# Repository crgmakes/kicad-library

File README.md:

# CRG Makes KiCad Library

This repo contains all the KiCad symbols, footprints, models, and other files supporting [CRG Makes](https://crgmakes.com) development within KiCad.

## Installation

To install this library, start by [cloning](https://docs.github.com/en/repositories/creating-and-managing-repositories/cloning-a-repository) the [CRG Makes libary](https://github.com/crgmakes/kicad-library) repo to a convienent local directory.

In this example, our local directory will be: `/Users/Development/KiCad/CRGM/`. 

<div class="alert alert-info">
  <i class="fas fa-exclamation-triangle"></i> <strong>Note:</strong> Replace this value with absolute path of where you place <b><i>your</i></b> library.
</div>

Start by setting the base parameters, the schematic parameters, and finally PCB parameters.

### Set Base Parameters

Within KiCad Project viewer:

Click on Preferences->Configure Paths...

Perform the following actions:

1. Click "+" near the bottom
1. Type "KICAD_USER_LIBRARY" in the first cell
1. Paste the local location repo's root directory (i.e., `/Users/Development/KiCad/CRGM/`)
1. Click "+" near the bottom
1. In the first cell, type "KICAD_USER_MODEL_DIR"
1. In the second cell, paste "${KICAD_USER_LIBRARY}/models"
1. Click "+" near the bottom
1. In the first cell, type "KICAD_USER_TEMPLATE_DIR"
1. In the second cell, paste "${KICAD_USER_LIBRARY}/templates"

Your screen should look something like this:

Click OK to save.

### Schematic

Within KiCad Schematic Editor, click Preferences->Manage Symbol Libraries...

Add the following parameters by clicking +:

<table class="table table-bordered">
  <thead class="thead-light">
    <tr>
      <th>Name</th>
      <th>Value</th>
    </tr>
  </thead>
  <tbody>
    <tr>
      <td>CRG Makes</td>
      <td>${KICAD_USER_LIBRARY}/symbols/CRG Makes.kicad_sym</td>
    </tr>
    <tr>
      <td>CRGM Connector</td>
      <td>${KICAD_USER_LIBRARY}/symbols/CRGM Connector.kicad_sym</td>
    </tr>
    <tr>
      <td>CRGM Logos</td>
      <td>${KICAD_USER_LIBRARY}/symbols/CRG Makes.kicad_sym</td>
    </tr>
    <tr>
      <td>CRGM Labels</td>
      <td>${KICAD_USER_LIBRARY}/symbols/CRGM Labels.kicad_sym</td>
    </tr>
    <tr>
      <td>CRGM Power</td>
      <td>${KICAD_USER_LIBRARY}/symbols/CRGM Power.kicad_sym</td>
    </tr>
    <tr>
      <td>CRGM Passive</td>
      <td>${KICAD_USER_LIBRARY}/symbols/CRGM Passive.kicad_sym</td>
    </tr>
    <tr>
      <td>CRGM Symbols</td>
      <td>${KICAD_USER_LIBRARY}/symbols/CRGM Symbols.kicad_sym</td>
    </tr>
    <tr>
      <td>CRGM Switches</td>
      <td>${KICAD_USER_LIBRARY}/symbols/CRGM Switches.kicad_sym</td>
    </tr>
  </tbody>
</table>

Your parameters should look like this:

### PCB

Within KiCad PCB Editor, click Preferences->Manage Footprint Libraries...

Add the following parameters by clicking +:

<table class="table table-bordered">
  <thead class="thead-light">
    <tr>
      <th>Name</th>
      <th>Value</th>
    </tr>
  </thead>
  <tbody>
    <tr>
      <td>CRG Makes</td>
      <td>${KICAD_USER_LIBRARY}/footprints/CRG Makes.pretty</td>
    </tr>
    <tr>
      <td>CRGM Connector</td>
      <td>${KICAD_USER_LIBRARY}/footprints/CRGM Connector.pretty</td>
    </tr>
    <tr>
      <td>CRGM Logos</td>
      <td>${KICAD_USER_LIBRARY}/footprints/CRG Makes.pretty</td>
    </tr>
    <tr>
      <td>CRGM Labels</td>
      <td>${KICAD_USER_LIBRARY}/footprints/CRGM Labels.pretty</td>
    </tr>
    <tr>
      <td>CRGM Mechanical</td>
      <td>${KICAD_USER_LIBRARY}/footprints/CRGM Mechanical.pretty</td>
    </tr>
    <tr>
      <td>CRGM Power</td>
      <td>${KICAD_USER_LIBRARY}/footprints/CRGM Power.pretty</td>
    </tr>
    <tr>
      <td>CRGM Passive</td>
      <td>${KICAD_USER_LIBRARY}/footprints/CRGM Passive.pretty</td>
    </tr>
    <tr>
      <td>CRGM Switches</td>
      <td>${KICAD_USER_LIBRARY}/footprints/CRGM Switches.pretty</td>
    </tr>
    <tr>
      <td>CRGM Symbols</td>
      <td>${KICAD_USER_LIBRARY}/footprints/CRGM Symbols.pretty</td>
    </tr>
  </tbody>
</table>

<div class="alert alert-info">
  <i class="fas fa-info-circle"></i> <strong>Note:</strong> PCB has a mechanical footprint library without a corresponding symbol library.
</div>

Your parameters should look like this:

### Models

You may need to manually set the model path for some footprints. You do so by opening the footprint's properties by couple clicking on the footprint in the PCB editor. 

Select 3D Models from the title bar:

Set the value to: `${KICAD_USER_MODEL_DIR}/{your model}`

Don't for get to select "Show" or your model will not display in 3d mode.

Happy making!

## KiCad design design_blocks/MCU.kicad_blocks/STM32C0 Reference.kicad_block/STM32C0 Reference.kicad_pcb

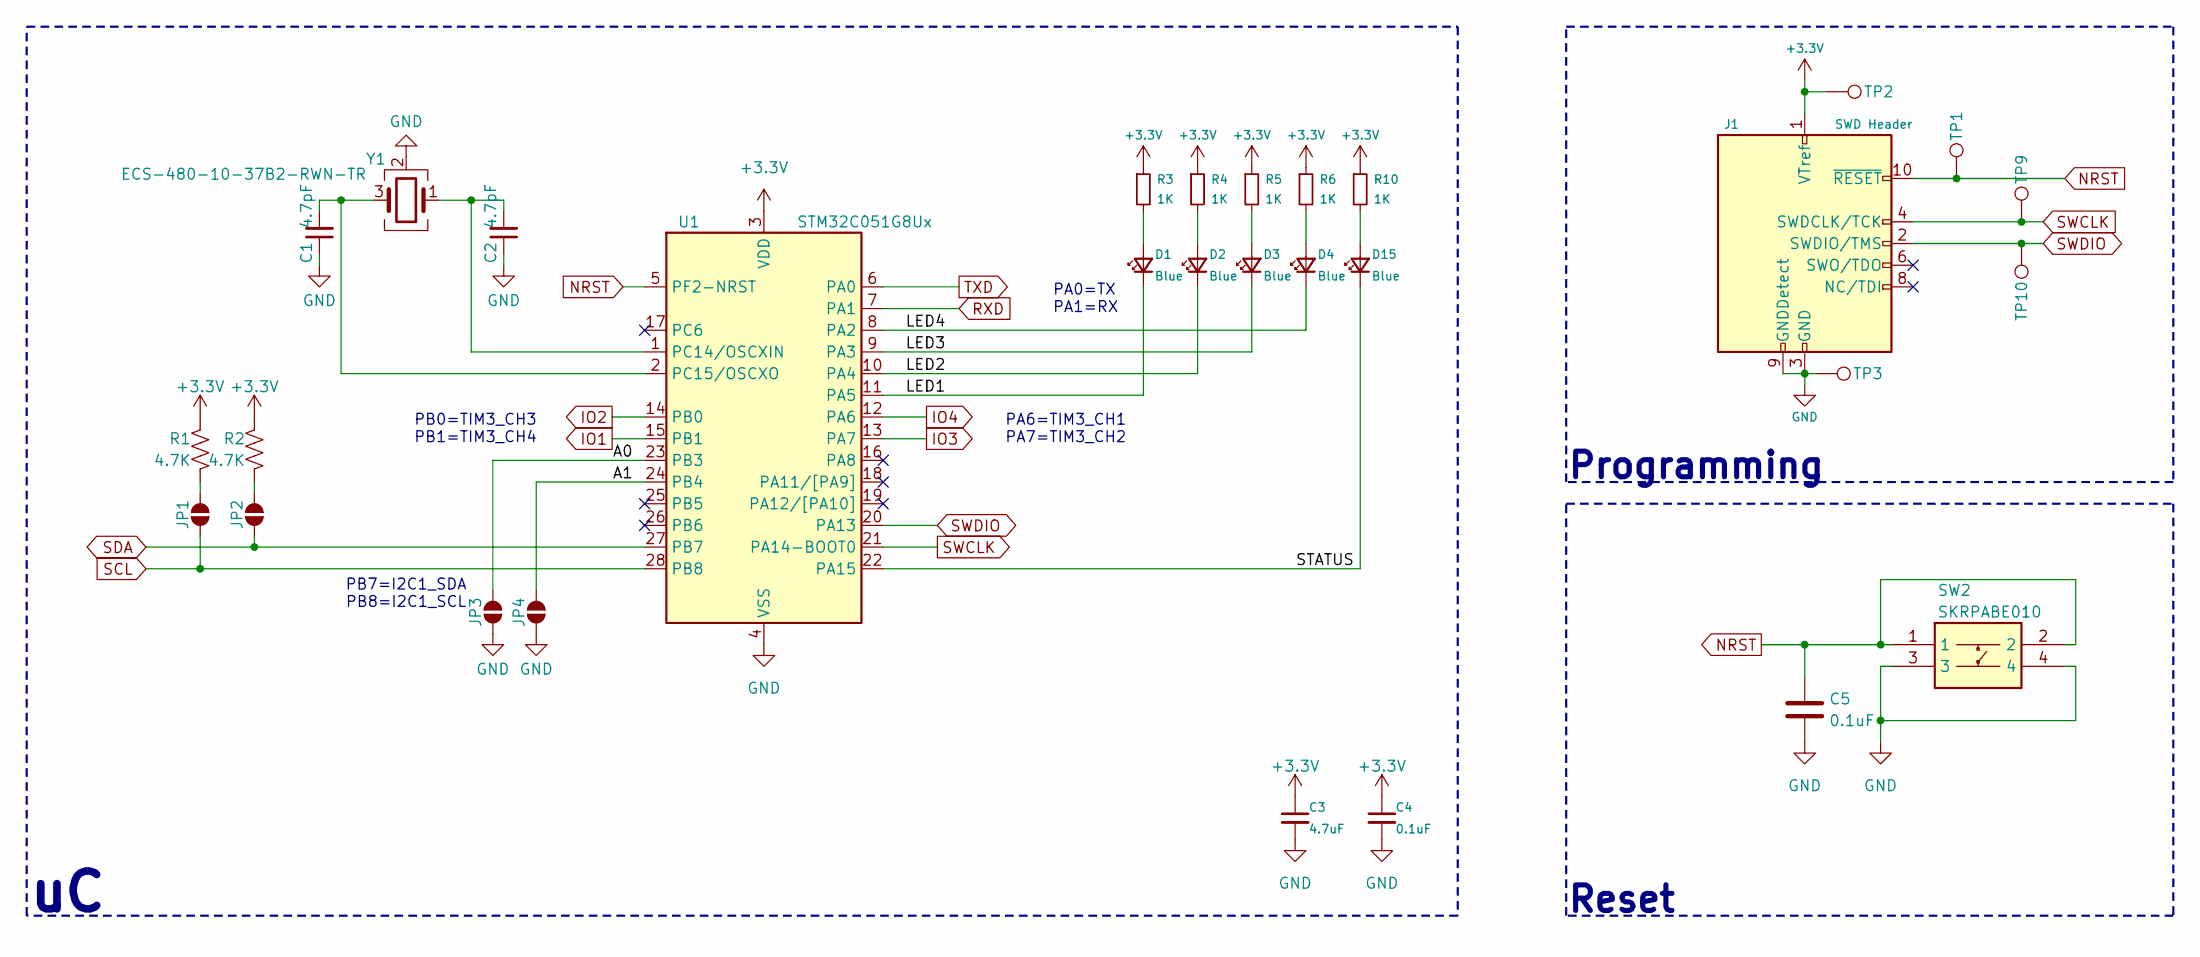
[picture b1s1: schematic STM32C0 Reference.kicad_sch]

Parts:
C1, C2: 4.7pF; C_0603_1608Metric; MPN FCC0603N4R7C500CT; Digikey 1276-1792-2-ND
C3: 4.7uF; C_0603_1608Metric; Tolerance 10%; MPN CL10A475KO8NNNC; Digikey 1276-1784-2-ND
C4: 0.1uF; C_0603_1608Metric; Tolerance 10%; MPN CL10B104KO8NNNC; Mouser 187-CL10B104KO8NNNC
C5: 0.1uF; C_0603_1608Metric; Tolerance 10%; MPN CL10B104KO8NNNC; Digikey 1276-1005-2-ND
D1, D2, D3, D4, D15: Blue; LED_0603_1608Metric; MPN XL-1608UBC-04; Digikey 5962-XL-1608UBC-04TR-ND
J1: SWD Header; PinHeader_2x05_P1.27mm_Vertical_SMD; MPN DZ127S-22-10-55; LCSC C5160761
JP1, JP2, JP3, JP4: SolderJumper_2_Open; SolderJumper-2_P1.3mm_Open_RoundedPad1.0x1.5mm
R1, R2: 4.7K; R_0603_1608Metric; Tolerance 5%; MPN FRC0603J472 TS; Mouser 71-CRCW06034K70JNEAC
R3, R4, R5, R6, R10: 1K; R_0603_1608Metric; Tolerance 5%; MPN FRC0603J102 TS; Mouser 71-CRCW06031K00JNEAC
SW2: SKRPABE010; SMD-4P-4.2x3.2mm; MPN SKRPABE010; Digikey 4809-SKRPABE010TR-ND
TP1, TP2, TP3, TP9, TP10: TestPoint_Pad_D1.0mm
U1: STM32C051G8Ux; QFN-28_4x4mm_P0.5mm; Digikey 497-STM32C051G8U6-ND
Y1: ECS-480-10-37B2-RWN-TR; Crystal_SMD_2016-4Pin_2.0x1.6mm; MPN ECS-480-10-37B2-RWN-TR; Digikey 50-ECS-480-10-37B2-RWN-TR-ND

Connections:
+3.3V: C3.1, C4.1, J1.1 (VTref), R1.2, R2.2, R3.1, R4.1, R5.1, R6.1, R10.1, TP2.1 (1_1), U1.3 (VDD)
/MCU/A0: JP3.2 (B), U1.23 (PB3)
/MCU/A1: JP4.2 (B), U1.24 (PB4)
/MCU/LED1: D1.1 (K), U1.11 (PA5)
/MCU/LED2: D2.1 (K), U1.10 (PA4)
/MCU/LED3: D3.1 (K), U1.9 (PA3)
/MCU/LED4: D4.1 (K), U1.8 (PA2)
/MCU/STATUS: D15.1 (K), U1.22 (PA15)
GND: C1.1, C2.1, C3.2, C4.2, C5.2, J1.3 (GND), J1.5 (GND), J1.9 (GNDDetect), JP3.1 (A), JP4.1 (A), TP3.1 (1_1), U1.4 (VSS), Y1.2 (G), Y1.4 (G); also elsewhere on the board
IO1: U1.15 (PB1)
IO2: U1.14 (PB0)
IO3: U1.13 (PA7)
IO4: U1.12 (PA6)
NRST: C5.1, J1.10 (~RESET), TP1.1 (1_1), U1.5 (PF2-NRST); also elsewhere on the board
unnamed: D1.2 (A), R3.2
unnamed: D2.2 (A), R4.2
unnamed: D3.2 (A), R5.2
unnamed: D4.2 (A), R6.2
unnamed: D15.2 (A), R10.2
unnamed: JP1.2 (B), R1.1
unnamed: JP2.2 (B), R2.1
unnamed: C2.2, U1.1 (PC14/OSCXIN), Y1.1
unnamed: C1.2, U1.2 (PC15/OSCXO), Y1.3
RXD: U1.7 (PA1)
SCL: JP1.1 (A), U1.28 (PB8)
SDA: JP2.1 (A), U1.27 (PB7)
SWCLK: J1.4 (SWDCLK/TCK), TP9.1 (1_1), U1.21 (PA14-BOOT0)
SWDIO: J1.2 (SWDIO/TMS), TP10.1 (1_1), U1.20 (PA13)
TXD: U1.6 (PA0)

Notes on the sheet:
PB0=TIM3_CH3 PB1=TIM3_CH4
PA6=TIM3_CH1 PA7=TIM3_CH2
Reset
Programming
PB7=I2C1_SDA PB8=I2C1_SCL
PA0=TX PA1=RX

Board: 4 copper layers, 30 parts (7 on the bottom side), 23 nets, no tracks yet.

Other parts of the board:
SW1: SKRPABE010; SMD-4P-4.2x3.2mm

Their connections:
GND: SW1.3, SW1.4; also elsewhere on the board
NRST: SW1.1, SW1.2; also elsewhere on the board

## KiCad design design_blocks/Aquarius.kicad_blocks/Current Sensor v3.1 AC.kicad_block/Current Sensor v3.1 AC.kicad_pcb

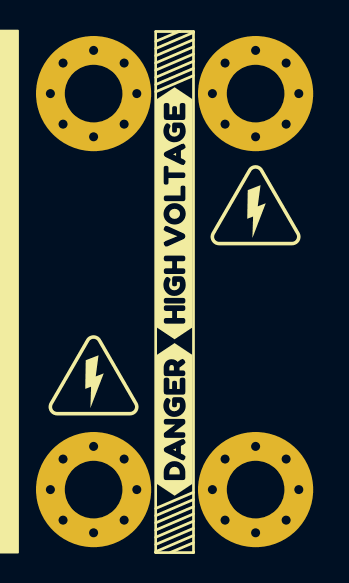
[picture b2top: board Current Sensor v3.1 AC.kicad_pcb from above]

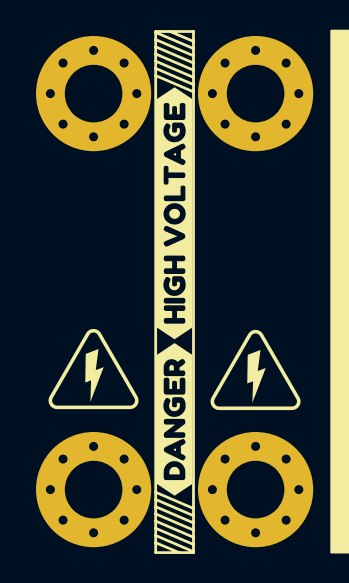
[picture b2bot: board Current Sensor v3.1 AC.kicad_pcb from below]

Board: 4 copper layers, 12 parts (4 on the bottom side), 2 nets, no tracks yet.

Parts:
H5, H6, H7, H8: MountingHole_3.2mm_M3_Pad_Via
SYM1, SYM2, SYM3, SYM4: HIGH-VOLTAGE-5MM
kibuzzard-68F7E62B: G***; kibuzzard-68F7E62B
kibuzzard-68F7E82B: G***; kibuzzard-68F7E82B
kibuzzard-68F7E620: G***; kibuzzard-68F7E620
kibuzzard-68F7E835: G***; kibuzzard-68F7E835

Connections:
/Power/Line: H5.1, H6.1
/Power/Neutral: H7.1, H8.1

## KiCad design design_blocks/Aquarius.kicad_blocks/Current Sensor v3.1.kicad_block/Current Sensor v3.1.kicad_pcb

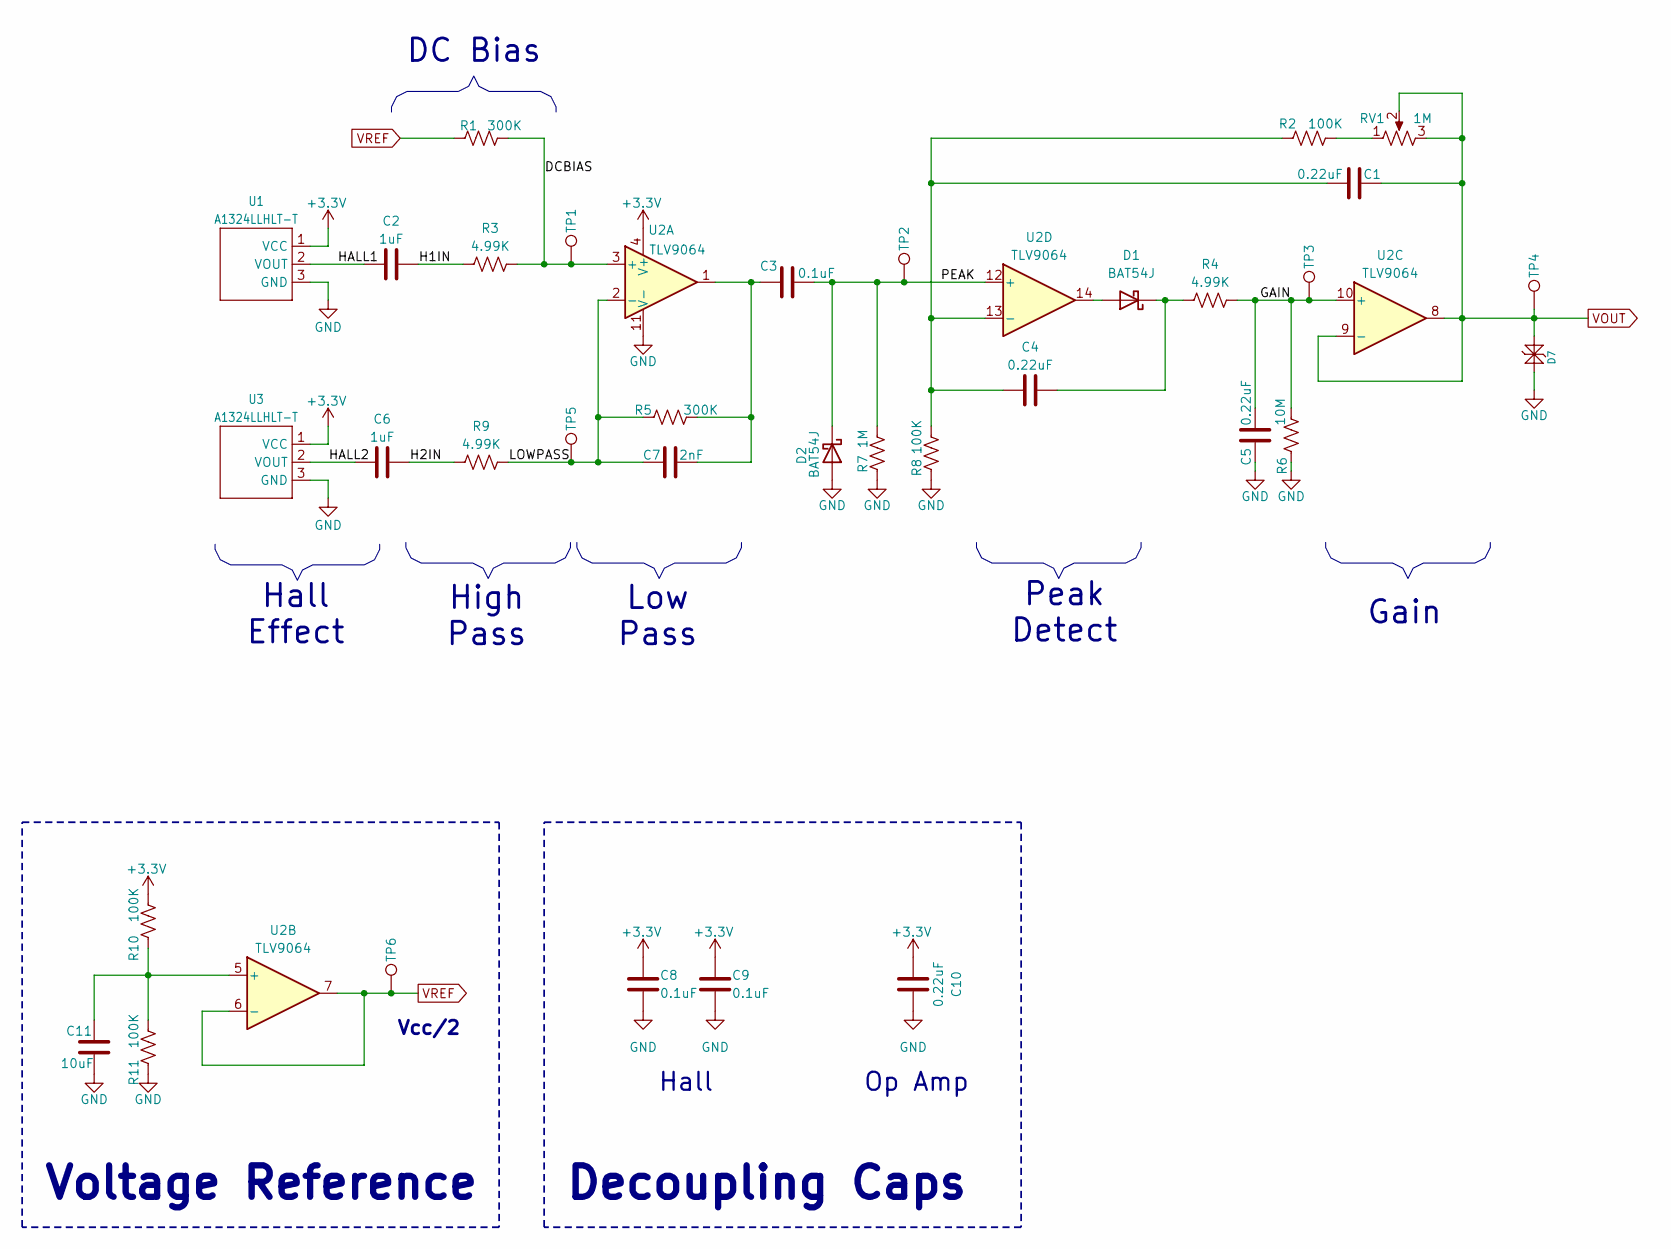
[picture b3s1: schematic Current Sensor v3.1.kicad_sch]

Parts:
C1, C4, C5, C10: 0.22uF; C_0603_1608Metric; Tolerance 10%; MPN CL10B224KA8NNNC; Mouser 603-CC603KRX7R8BB224
C2, C6: 1uF; C_0603_1608Metric; Tolerance 10%; MPN CGA0603X5R105K160JT; Digikey 1276-1019-2-ND
C3, C8, C9: 0.1uF; C_0603_1608Metric; Tolerance 10%; MPN CL10B104KO8NNNC; LCSC C66501
C7: 2nF; C_0603_1608Metric; Tolerance 10%; MPN CC0603KRX7R9BB202; Mouser 603-CC603KRX7R9BB202
C11: 10uF; C_0603_1608Metric; Tolerance 10%; MPN CL10A106MO8NQNC; Mouser 187-CL10A106MO8NQNC
D1, D2: BAT54J; D_SOD-323F; MPN BAT54J,115; Mouser 771-BAT54J115
D7: PESD3V3S1BL; DFN1006-2; MPN LESD8D3.3CAT5G; LCSC C5563754
R1, R5: 300K; R_0603_1608Metric; Tolerance 5%; MPN FRC0603F3003TS; Digikey CR0603-JW-304ELFTR-ND
R2, R8, R10, R11: 100K; R_0603_1608Metric; Tolerance 5%; MPN FRC0603F1003TS; Digikey CR0603-JW-104ELFTR-ND
R3, R4, R9: 4.99K; R_0603_1608Metric; Tolerance 1%; MPN FRC0603F4991TS; Digikey 541-4.99KHTR-ND
R6: 10M; R_0603_1608Metric; Tolerance 5%; MPN FRC0603J106 TS; Digikey CR0603-JW-106ELFTR-ND
R7: 1M; R_0603_1608Metric; Tolerance 5%; MPN FRC0603F1003TS; Digikey CR0603-JW-105ELFTR-ND
RV1: 1M; Bourns_TC33X_Vertical; Tolerance 25%; MPN TC33X-2-105E; Mouser 652-TC33X-2-105E
TP1, TP2, TP3, TP4, TP5, TP6: TestPoint_Pad_D1.0mm
U1, U3: A1324LLHLT-T; SOT23W; MPN A1324LLHLT-T; Mouser 250-A1324LLHLX-T
U2: TLV9064; SOIC-14_3.9x8.7mm_P1.27mm; MPN TLV9064IDR; Mouser 595-TLV9064IDR

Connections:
+3.3V: C8.1, C9.1, C10.1, R10.1, U1.1 (VCC), U2.4 (V+), U3.1 (VCC)
/Current Sensor/DCBIAS: R1.1, R3.1, TP1.1, U2.3 (+)
/Current Sensor/GAIN: C5.2, R4.1, R6.1, TP3.1, U2.10 (+)
/Current Sensor/H1IN: C2.2, R3.2
/Current Sensor/H2IN: C6.2, R9.2
/Current Sensor/HALL1: C2.1, U1.2 (VOUT)
/Current Sensor/HALL2: C6.1, U3.2 (VOUT)
/Current Sensor/LOWPASS: C7.1, R5.2, R9.1, TP5.1, U2.2 (-)
/Current Sensor/PEAK: C3.2, D2.1 (K), R7.1, TP2.1, U2.12 (+)
GND: C5.1, C8.2, C9.2, C10.2, C11.2, D2.2 (A), D7.1 (K1), R6.2, R7.2, R8.2, R11.2, U1.3 (GND), U2.11 (V-), U3.3 (GND)
unnamed: C3.1, C7.2, R5.1, U2.1
unnamed: D1.2 (A), U2.14
unnamed: C4.2, D1.1 (K), R4.2
unnamed: R2.1, RV1.1
unnamed: C11.1, R10.2, R11.1, U2.5 (+)
unnamed: C1.1, C4.1, R2.2, R8.1, U2.13 (-)
VOUT: C1.2, D7.2 (K2), RV1.2, RV1.3, TP4.1, U2.8, U2.9 (-)
VREF: R1.2, TP6.1, U2.6 (-), U2.7

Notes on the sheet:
High Pass
Hall Effect
DC Bias
Gain
Low Pass
Op Amp
Vcc/2
Decoupling Caps
Voltage Reference
Peak Detect
Hall

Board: 4 copper layers, 35 parts (6 on the bottom side), 18 nets, no tracks yet.

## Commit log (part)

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2025-05-17 initial checkin
2025-05-17 Initial checkin of library files
2025-05-17 Finished first draft of install instructions.
2025-05-20 updated module to adjust origins.
2025-05-26 updated footprints for kicad positions
2025-05-29 Added soldermask to pins
2025-06-02 Added additional parts; fixed origin of other parts
    Added new design blocks
2025-06-07 updated ESP32-S3 footprint attributes
2025-06-09 Added UDPI Symbol and 2x3 SMD footprint
2025-06-21 Pulled some footprints into CRM
2025-06-21 Added mounting holes
2025-06-23 added 8mm logos
2025-06-26 Updated frame template
2025-06-27 Updated worksheet template
2025-06-28 Updated footprints for DFM; added FUET and XF2M
2025-07-12 renames models for consistency; deleted unused models
2025-07-24 Updated license; added foot prints and 3d models
2025-08-11 Moved stock parts to CRGM libraries
2025-08-12 added symbol and footprint for VOC sensor
2025-08-12 Removed unused footprints; fixed models for many components
2025-08-14 Added 3.5mm CRGM logo
2025-08-15 Added Bourns Pot
2025-08-16 fixed axis
2025-08-16 Added 0603 Resistor and Capacitor
2025-08-16 Fixed pot model and footprint
2025-08-23 Cleaned up logos; made consistent; added Roxy
2025-08-23 Fixed footprint on LED block; added Roxy 6.5
2025-08-25 Added SOIC14 to CRGM
2025-08-25 Added LED, Bourns, SOD-323, SOT-23
2025-08-26 Updated model; added SOT666
    Updated model and offset of JST SH BM04
    Added SOT-666
2025-08-26 Fixed default models; fixed USBLC6
2025-08-28 added test point property to test point pad
2025-08-31 Fixed rotation of TO-242; added SRX883 and STX883
2025-09-01 Updated properties for consistency
2025-09-02 Updated text size
    Added QFN-28
    Added SOT-523
2025-09-06 Updated model paths
2025-09-06 Fixed model directory
2025-10-18 Updated reference designators
2025-10-22 Updated blocks
    Added current sensor
    Updated LEDs
    Updated QWICC
    Changed MCU
2025-10-24 Added i2c switch
2025-10-28 Added JST SH BM06
    Fixed model for BM03
    Added 4.2x3.2 switch
2025-11-02 Changed pin 1 indicator on SON80 footprint
2025-11-03 Added mechanical symbols
2025-11-04 Added AHT20
    Added BAT48 model
    DFM updates
2025-11-04 Fixed model on SGP40
    Updated silkscreen line width to be 0.15mm min
2025-11-05 Updated footprints for DFM
2025-11-18 changed fab designator location
2025-11-25 added 1206 capacitor footprint
2025-12-16 Added new footprints
    Added 6.3x54. electrolytic cap
    Added Sunlord Inductor
2025-12-27 Updated fab drawing for TO-252
2025-12-29 Added foot print for opto-isolator
    Added symbol for opto-isolator
    Added symbol for open jumper
2026-01-01 Added new blocks and footprints
    Added Blue LED power blokc
    Added 2.0mm pitch jumper
    Added 5x5.4 Cap
    Added SM02B model
    Updated DFN1006 to have ref designator on fab layer
2026-01-01 Updated silkscreen on 2.0mm jumper
2026-01-02 Created new logo sizes
    Aquarius 3.5mm
    Roxy 4mm
2026-02-03 Added new UPDI UART symbol
2026-02-18 Added N16R2
2026-02-27 Updated logos and added WS2812 2020
2026-03-01 replaced .wrl with .step
2026-03-06 Made mounting points ground enabled
2026-03-06 Renamed step files to lower case
2026-03-06 Added N16R2 model
2026-03-06 Updated model for ESP32-N16
    removed wrl file
    removed filter for esp32
2026-03-12 Updated footprints
2026-03-12 Changed footprint for LDO
2026-03-12 Validated footprints
2026-03-19 Added design blocks and model
2026-03-20 Updated A1324 origin
    Updated SOT23W model path
2026-03-22 Updated ATTINY1616 footprint
2026-04-15 Fixed attribute for UPDI footprint
2026-05-28 Cleaned JST SH02 and DFM1006
    Changed JST SH02 symbol point to CRGM Connectors
2026-06-10 Added new blocks, c_small, smt32c0
2026-06-10 Added SOD-882 model; default for DFN1006-2
2026-06-10 Added common models and added parts
2026-06-13 Added more footprints and symbols
    QFN-20-4x4
    Pin Header 1.27 2x05
    Crystal 1612
    Crystal 2016
    Models for crystal and SMT32C0
2026-06-13 Fixed path; added Crystal model
2026-06-15 fixed part numbers
2026-06-17 Added new models
